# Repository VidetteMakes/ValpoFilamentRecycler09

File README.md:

# ValpoFilamentRecycler09

 Valpo Filament Senior Design Project

Check out the documentation folder for more information.

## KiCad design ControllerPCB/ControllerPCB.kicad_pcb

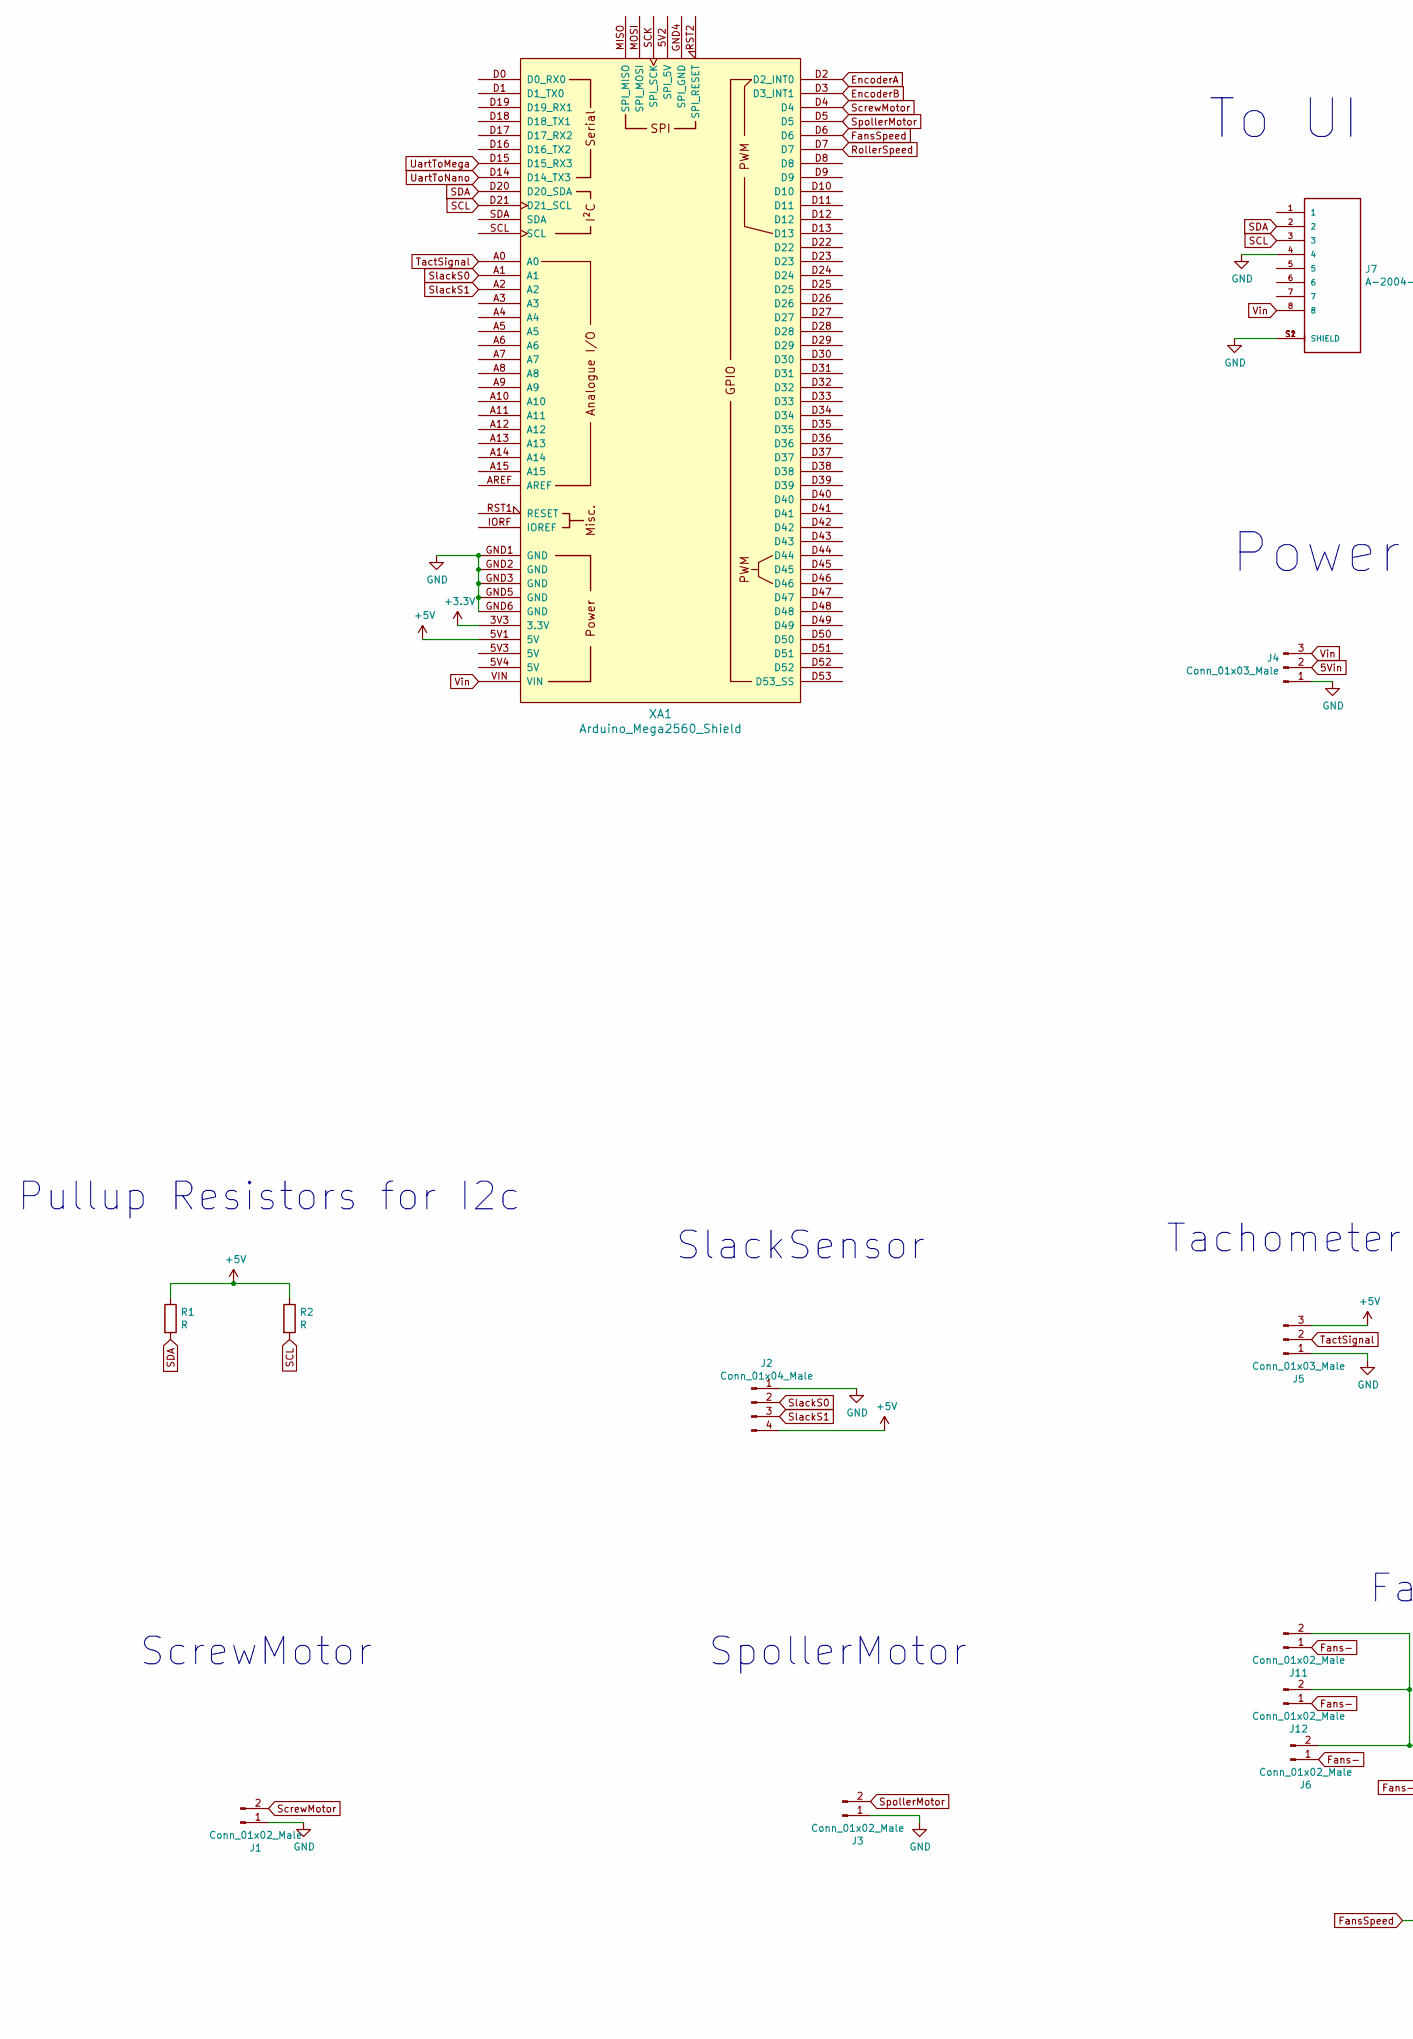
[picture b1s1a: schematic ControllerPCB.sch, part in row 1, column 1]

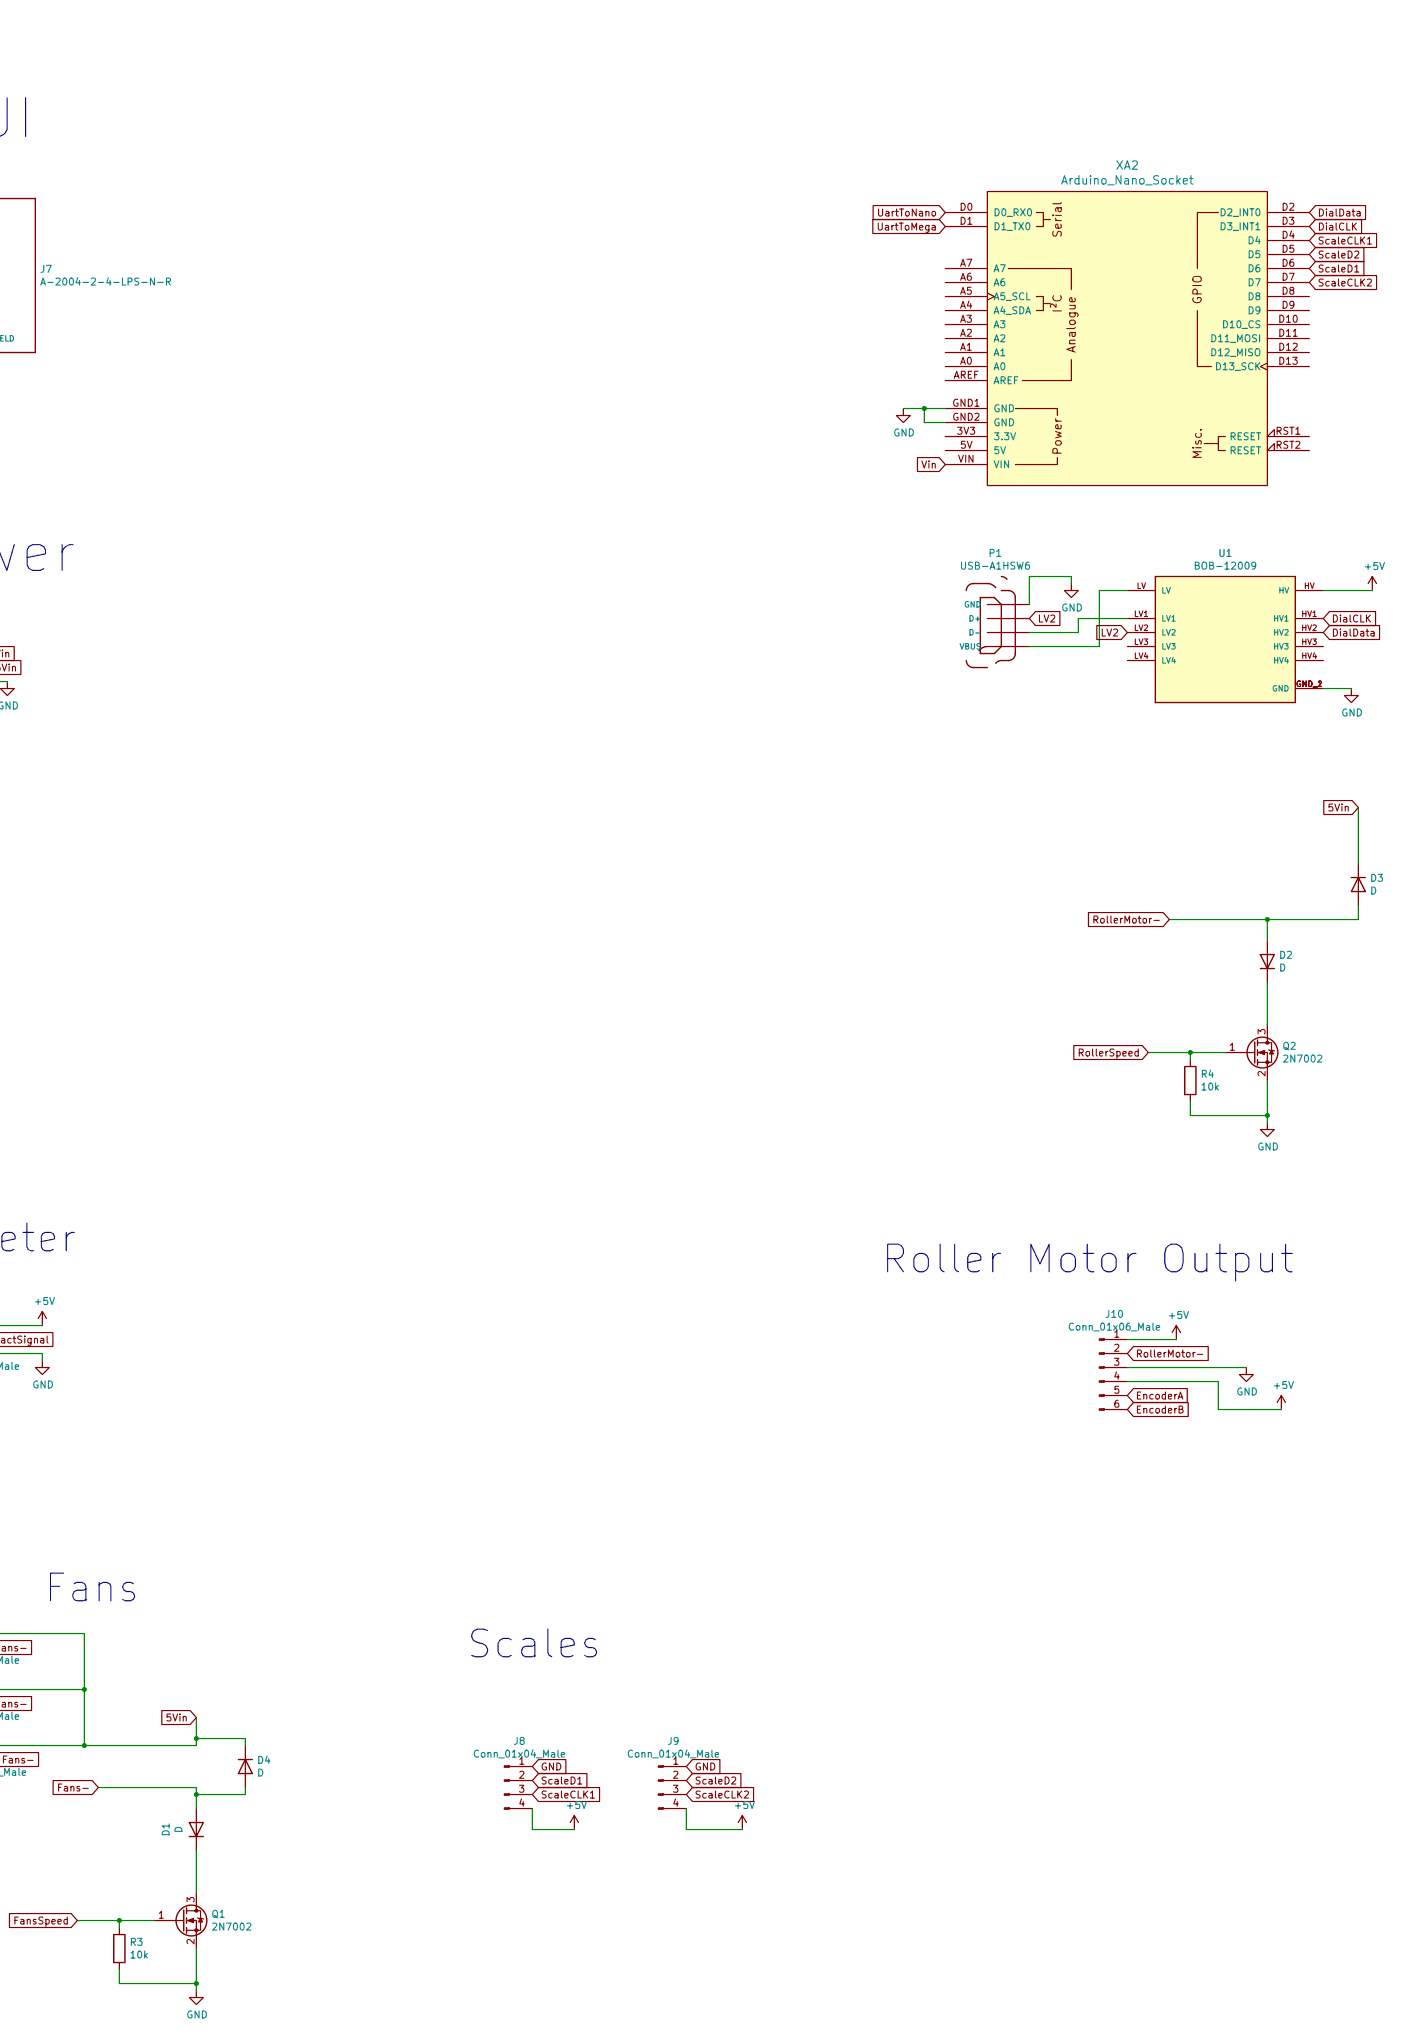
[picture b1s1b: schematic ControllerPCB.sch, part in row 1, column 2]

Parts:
D1, D2, D3, D4: D; D_DO-15_P15.24mm_Horizontal
J1, J3, J6, J11, J12: Conn_01x02_Male; PinHeader_1x02_P2.54mm_Vertical
J2, J8, J9: Conn_01x04_Male; PinHeader_1x04_P2.54mm_Vertical
J4, J5: Conn_01x03_Male; PinHeader_1x03_P2.54mm_Vertical
J7: A-2004-2-4-LPS-N-R; ASSMANN_A-2004-2-4-LPS-N-R; PARTREV 00
J10: Conn_01x06_Male; PinHeader_1x06_P2.54mm_Vertical
P1: USB-A1HSW6; OST_USB-A1HSW6
Q1, Q2: 2N7002; PinHeader_1x03_P2.54mm_Vertical
R1, R2: R; R_Axial_DIN0207_L6.3mm_D2.5mm_P10.16mm_Horizontal
R3, R4: 10k; R_Axial_DIN0207_L6.3mm_D2.5mm_P10.16mm_Horizontal
U1: BOB-12009; CONV_BOB-12009; PARTREV 01
XA1: Arduino_Mega2560_Shield
XA2: Arduino_Nano_Socket

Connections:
5Vin: D3.1 (K), D4.1 (K), J4.2, J6.2, J11.2, J12.2
+3V3: XA1.3V3 (3.3V)
+5V: J2.4, J5.3, J8.4, J9.4, J10.1, J10.4, R1.1, R2.1, U1.HV, XA1.5V1 (5V)
DialCLK: U1.HV1, XA2.D3 (D3_INT1)
DialData: U1.HV2, XA2.D2 (D2_INT0)
EncoderA: J10.5, XA1.D2 (D2_INT0)
EncoderB: J10.6, XA1.D3 (D3_INT1)
Fans-: D1.2 (A), D4.2 (A), J6.1, J11.1, J12.1
FansSpeed: Q1.1 (G), R3.1, XA1.D6
GND: J1.1, J2.1, J3.1, J4.1, J5.1, J7.4, J7.S1 (SHIELD), J7.S2 (SHIELD), J8.1, J9.1, J10.3, P1.4 (GND), Q1.2 (S), Q2.2 (S), R3.2, R4.2, U1.GND_1 (GND), U1.GND_2 (GND), XA1.GND1 (GND), XA1.GND2 (GND), XA1.GND3 (GND), XA1.GND5 (GND), XA1.GND6 (GND), XA2.GND1 (GND), XA2.GND2 (GND)
LV2: P1.3 (D+), U1.LV2
unnamed: D1.1 (K), Q1.3 (D)
unnamed: D2.1 (K), Q2.3 (D)
unnamed: P1.1 (VBUS), U1.LV
unnamed: P1.2 (D-), U1.LV1
RollerMotor-: D2.2 (A), D3.2 (A), J10.2
RollerSpeed: Q2.1 (G), R4.1, XA1.D7
SCL: J7.3, R2.2, XA1.D21 (D21_SCL)
SDA: J7.2, R1.2, XA1.D20 (D20_SDA)
ScaleCLK1: J8.3, XA2.D4
ScaleCLK2: J9.3, XA2.D7
ScaleD1: J8.2, XA2.D6
ScaleD2: J9.2, XA2.D5
ScrewMotor: J1.2, XA1.D4
SlackS0: J2.2, XA1.A1
SlackS1: J2.3, XA1.A2
SpollerMotor: J3.2, XA1.D5
TactSignal: J5.2, XA1.A0
UartToMega: XA1.D15 (D15_RX3), XA2.D1 (D1_TX0)
UartToNano: XA1.D14 (D14_TX3), XA2.D0 (D0_RX0)
Vin: J4.3, J7.8, XA1.VIN, XA2.VIN

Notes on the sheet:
Pullup Resistors for I2c
SlackSensor
Tachometer
Roller Motor Output
ScrewMotor
SpollerMotor
Fans
Scales
Power
To UI

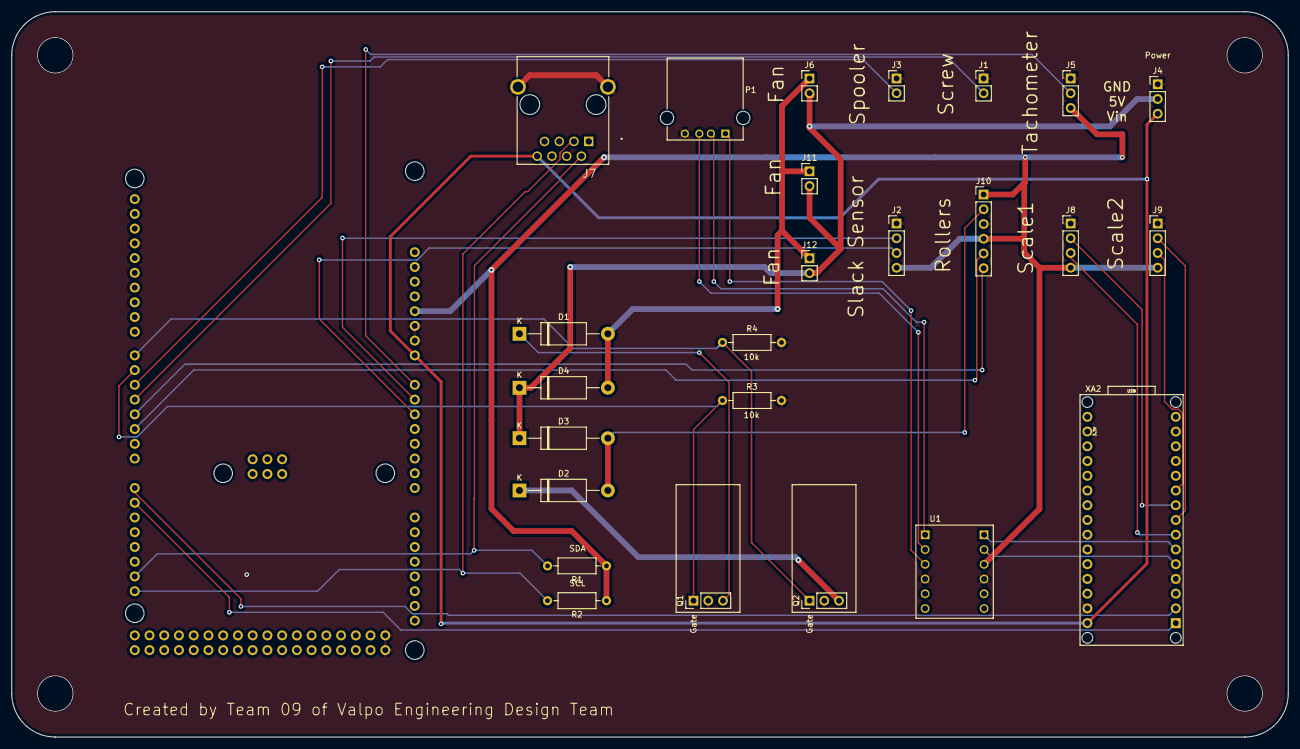
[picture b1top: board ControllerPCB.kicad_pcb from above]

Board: 2 copper layers, 220.0 x 125.0 mm, 26 parts (1 on the bottom side), 30 nets.

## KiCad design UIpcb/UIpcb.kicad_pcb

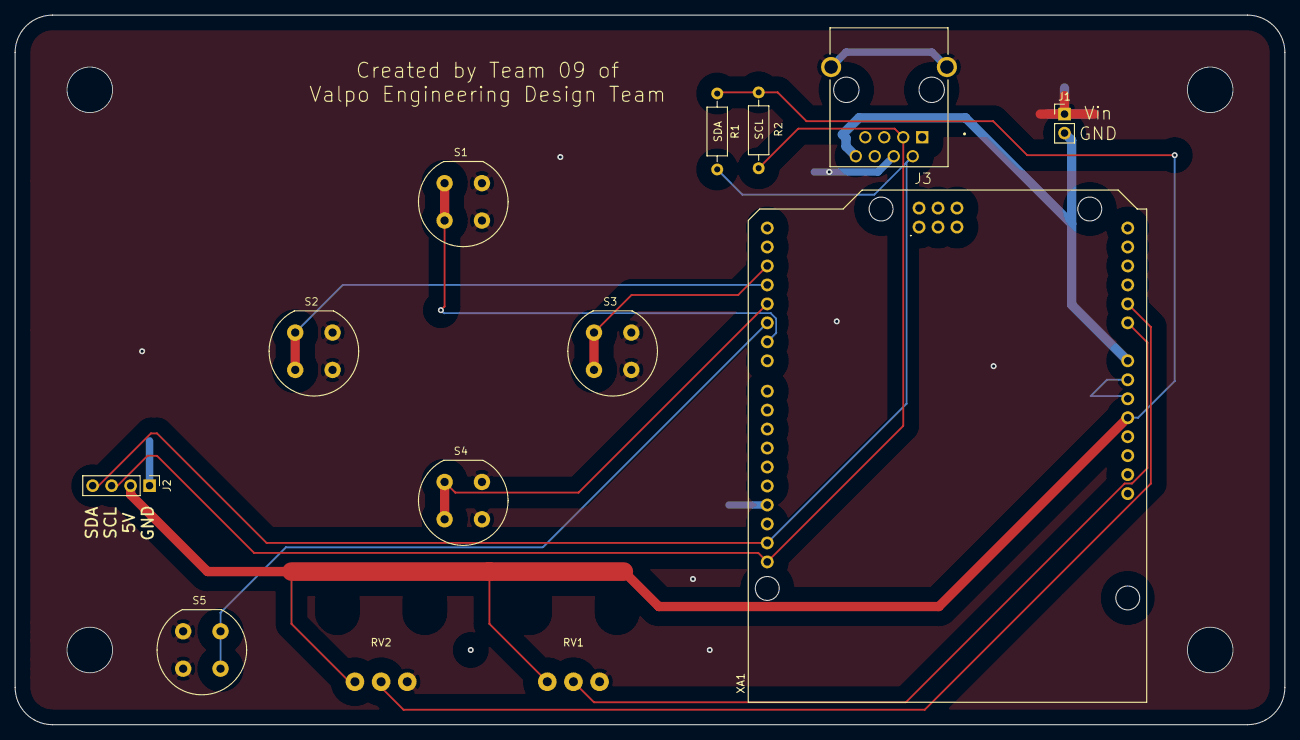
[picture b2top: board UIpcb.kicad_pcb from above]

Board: 2 copper layers, 170.0 x 95.0 mm, 13 parts (0 on the bottom side), 12 nets.

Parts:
J1: Conn_01x02_Male; PinHeader_1x02_P2.54mm_Vertical
J2: Conn_01x04_Male; PinHeader_1x04_P2.54mm_Vertical
J3: A-2004-2-4-LPS-N-R; ASSMANN_A-2004-2-4-LPS-N-R
R1, R2: R; R_Axial_DIN0207_L6.3mm_D2.5mm_P10.16mm_Horizontal
RV1, RV2: R_POT; P120PK
S1, S2, S3, S4, S5: D6R90_F1_LFS; SW_D6R90_F1_LFS
XA1: Arduino_Uno_Shield

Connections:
2: S3.1, S3.2, XA1.D2
3: S2.1, S2.2, XA1.D3
4: S4.1, S4.2, XA1.D4
5: S5.3, S5.4, XA1.D5
6: S1.1, S1.2, XA1.D6
+5V: J2.2, R1.1, R2.2, RV1.1, RV2.1, XA1.5V1
A0: RV1.2, XA1.A0
A1: RV2.2, XA1.A1
GND: J1.1, J2.1, J3.4, J3.S1, J3.S2, RV1.3, RV2.3, S1.3, S1.4, S2.3, S2.4, S3.3, S3.4, S4.3, S4.4, S5.1, S5.2, XA1.GND1, XA1.GND2, XA1.GND3
SCL: J2.3, J3.3, R2.1, XA1.SCL
SDA: J2.4, J3.2, R1.2, XA1.SDA
Vin: J1.2, J3.8, XA1.VIN

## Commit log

2020-10-15 Kicad Added
2020-10-16 Schematic Started
2020-10-17 Added first version of schematic
2020-10-18 Added Stuff
2021-04-20 Add PCB diagrams
    Added PCB boards for the controller and UI
2021-05-03 Added pdfs
2021-05-04 Fix Typo in Spooler
2021-05-10 Added Cad and documentation
2021-06-30 Trying to figure out what parts are in each sheet of the BOM.
2021-07-08 Continue updating BOM.
2021-07-08 Moving files.
2021-07-14 Updating BOM; there were some parts that were incorrect vs. what's actually used in the machines.
2021-07-14 Experimenting with Fritzing to create wiring diagrams.
2021-07-14 work on updating BOM.
2021-07-14 Updating BOM.
2021-07-14 Folder rename.
2021-07-14 Added a few components.
2021-07-14 Added datasheets.
2021-07-15 Added parts that we need to order to complete the machines.
2021-07-15 Schematic now fits on a letter size page. Output to PDF.
2021-07-15 Organized PCB files.
2021-07-15 Unsure if this file is important, so adding.
2021-07-15 Few have access to CorelDRAW, so I made a PDF.
2021-07-15 Updated BOM.
2021-07-16 Added datasheet for power connector.
2021-07-16 Added Fritzing "breadboard" diagram of UI components.
2021-07-16 Updated Extruder wiring diagram with parts.
2021-07-17 Organizing files.
2021-07-17 Converted files to open format.
2021-07-20 Made a note of connector type needed.
2021-07-22 Added hand-built circuit for spooler and fan motors.
2021-07-23 BOM updates.
2021-07-23 BOM much nicer!
2021-07-23 Moved files.
2021-07-24 Fan driver circuit corrections.
2021-07-24 Spooler Updates to BOM, Schematic.
2021-07-25 Added 12V to 5V DC/DC Converter.
2021-07-25 Spooler's fan driver circuit works! At least the right side circuit does. Left side is included in the controller PCB, so I didn't make it on a perfboard.
2021-08-04 Added adaptor PCB for small DC motor (not finished).
2021-08-04 BOM update.
2021-08-05 Starting to research properties of various plastics.
2022-08-29 Deleting old files that no longer represent the design.
2022-08-29 Updated controller PCB.
2022-08-29 Updated extruder PCB for latest KiCad version.
2022-08-29 Updating schematics for spooling machine.
2022-08-30 Removed potentiometers and Ethernet connector.
2023-03-14 Updated documents for Extruder v2.0. In progress.
2023-03-15 Added enclosure manufacturer info.
2024-01-28 Updating electronics to get closer to 3.0.
2024-01-28 Unsure...it's been a while.
